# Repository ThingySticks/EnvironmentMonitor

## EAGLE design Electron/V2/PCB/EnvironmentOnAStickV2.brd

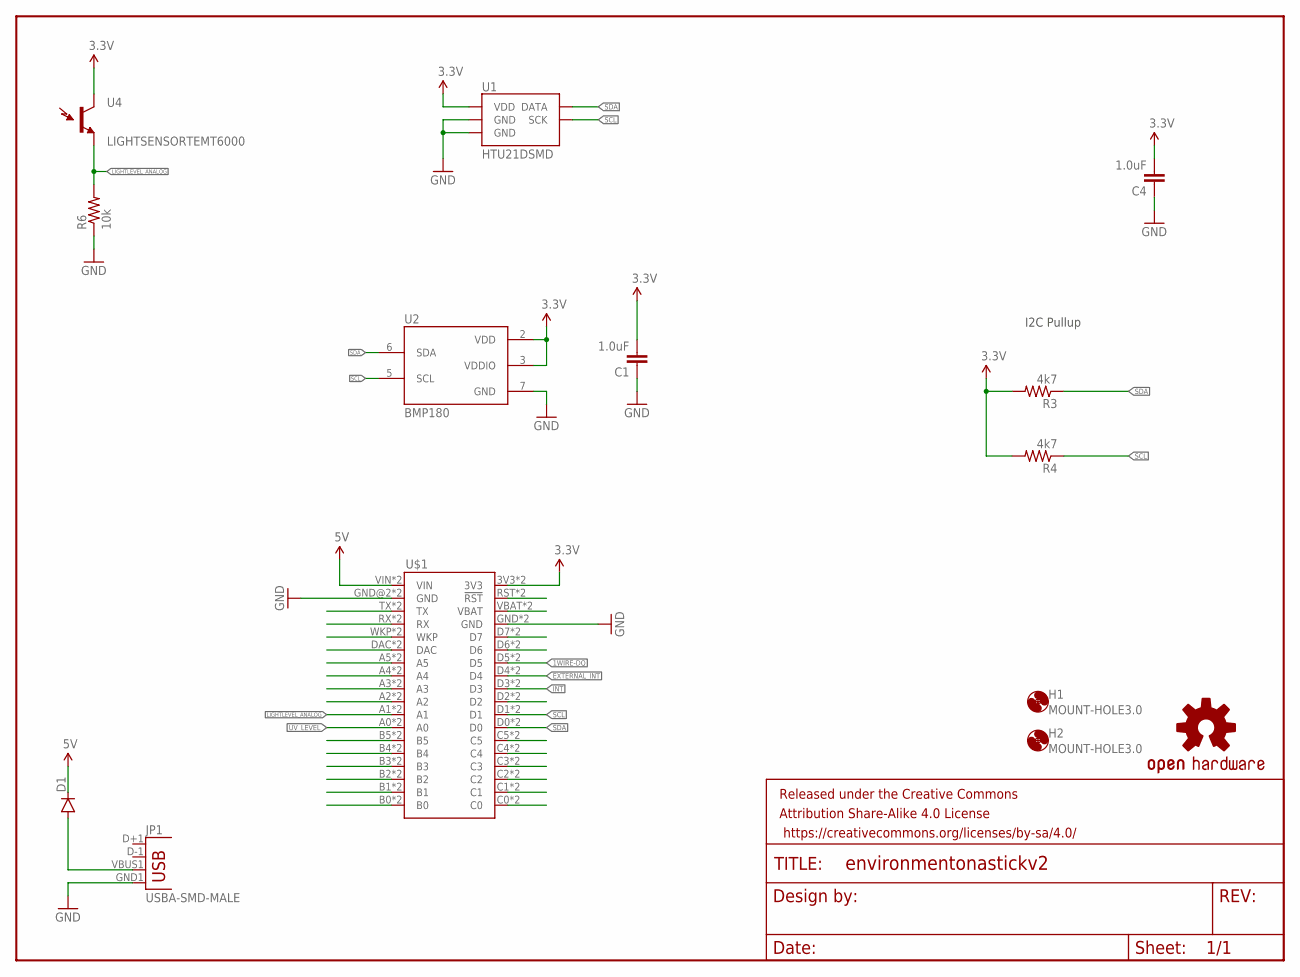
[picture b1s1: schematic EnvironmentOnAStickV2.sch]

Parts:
C1, C4: 1.0uF; 0805-CAP
D1: DIODESMA; SMA-DIODE
FRAME1: FRAME-LETTER; CREATIVE_COMMONS
H1, H2: MOUNT-HOLE3.0; 3,0
JP1: USBA-SMD-MALE; USB-A-SMT-MALE
LOGO1: OSHW-LOGOM; OSHW-LOGO-M
R3, R4: 4k7; 0805
R6: 10k; 0805
U1: HTU21DSMD; HTU21D
U2: BMP180
U4: LIGHTSENSORTEMT6000; TEMT6000-SEN
U$1: ELECTRONDUALNAMED; ELECTRON_SIMPLE_SILK_NAMES_DUAL

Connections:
1WIRE-DQ: U$1.D5, U$1.D5_1 (D5)
3.3V: C1.2, C4.2, R3.2, R4.2, U1.VDD, U2.2 (VDD), U2.3 (VDDIO), U4.COLLECTOR (C1), U$1.3V3, U$1.3V3_1 (3V3)
5V: D1.C, U$1.VIN, U$1.VIN_1B (VIN)
EXTERNAL_INT: U$1.D4, U$1.D4_1 (D4)
GND: C1.1, C4.1, JP1.GND1 (GND), R6.1, U1.7 (GND), U1.GND, U2.7 (GND), U$1.GND, U$1.GND@2 (GND), U$1.GND_1 (GND), U$1.GND_1B (GND)
INT: U$1.D3, U$1.D3_1 (D3)
LIGHTLEVEL_ANALOG: R6.2, U4.EMITTER (E1), U$1.A1, U$1.A1_1 (A1)
unnamed: U$1.RST (!RST), U$1.RST_1 (!RST)
unnamed: U$1.VBAT, U$1.VBATT_1 (VBAT)
unnamed: U$1.D7, U$1.D7_1 (D7)
unnamed: U$1.D6, U$1.D6_1 (D6)
unnamed: D1.A, JP1.VBUS1 (VBUS)
unnamed: U$1.D2, U$1.D2_1 (D2)
unnamed: U$1.C5, U$1.C5_1 (C5)
unnamed: U$1.C4, U$1.C4_1 (C4)
unnamed: U$1.C3, U$1.C3_1 (C3)
unnamed: U$1.C2, U$1.C2_1 (C2)
unnamed: U$1.C1, U$1.C1_1 (C1)
unnamed: U$1.C0, U$1.C0_1 (C0)
unnamed: U$1.B0, U$1.B0_1 (B0)
unnamed: U$1.B1, U$1.B1_1 (B1)
unnamed: U$1.B2, U$1.B2_1 (B2)
unnamed: U$1.B3, U$1.B3_1 (B3)
unnamed: U$1.B4, U$1.B4_1 (B4)
unnamed: U$1.B5, U$1.B5_1 (B5)
unnamed: U$1.A2, U$1.A2_1 (A2)
unnamed: U$1.A3, U$1.A3_1 (A3)
unnamed: U$1.A4, U$1.A4_1 (A4)
unnamed: U$1.A5, U$1.A5_1 (A5)
unnamed: U$1.DAC, U$1.DAC_1 (DAC)
unnamed: U$1.WKP, U$1.WKP_1 (WKP)
unnamed: U$1.RX, U$1.RX_1 (RX)
unnamed: U$1.TX, U$1.TX_1 (TX)
SCL: R4.1, U1.SCK, U2.5 (SCL), U$1.D1, U$1.D1_1 (D1)
SDA: R3.1, U1.DATA, U2.6 (SDA), U$1.D0, U$1.D0_1 (D0)
UV_LEVEL: U$1.A0, U$1.A0_1 (A0)

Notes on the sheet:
I2C Pullup

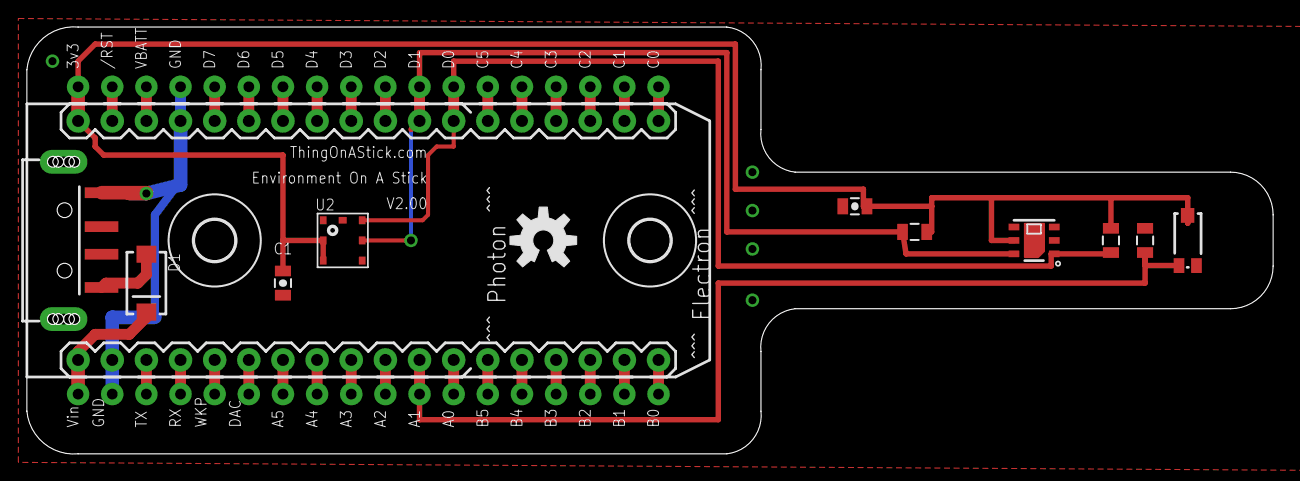
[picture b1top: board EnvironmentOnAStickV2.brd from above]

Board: 2 copper layers, 92.7 x 31.8 mm, 15 parts (0 on the bottom side), 36 nets.

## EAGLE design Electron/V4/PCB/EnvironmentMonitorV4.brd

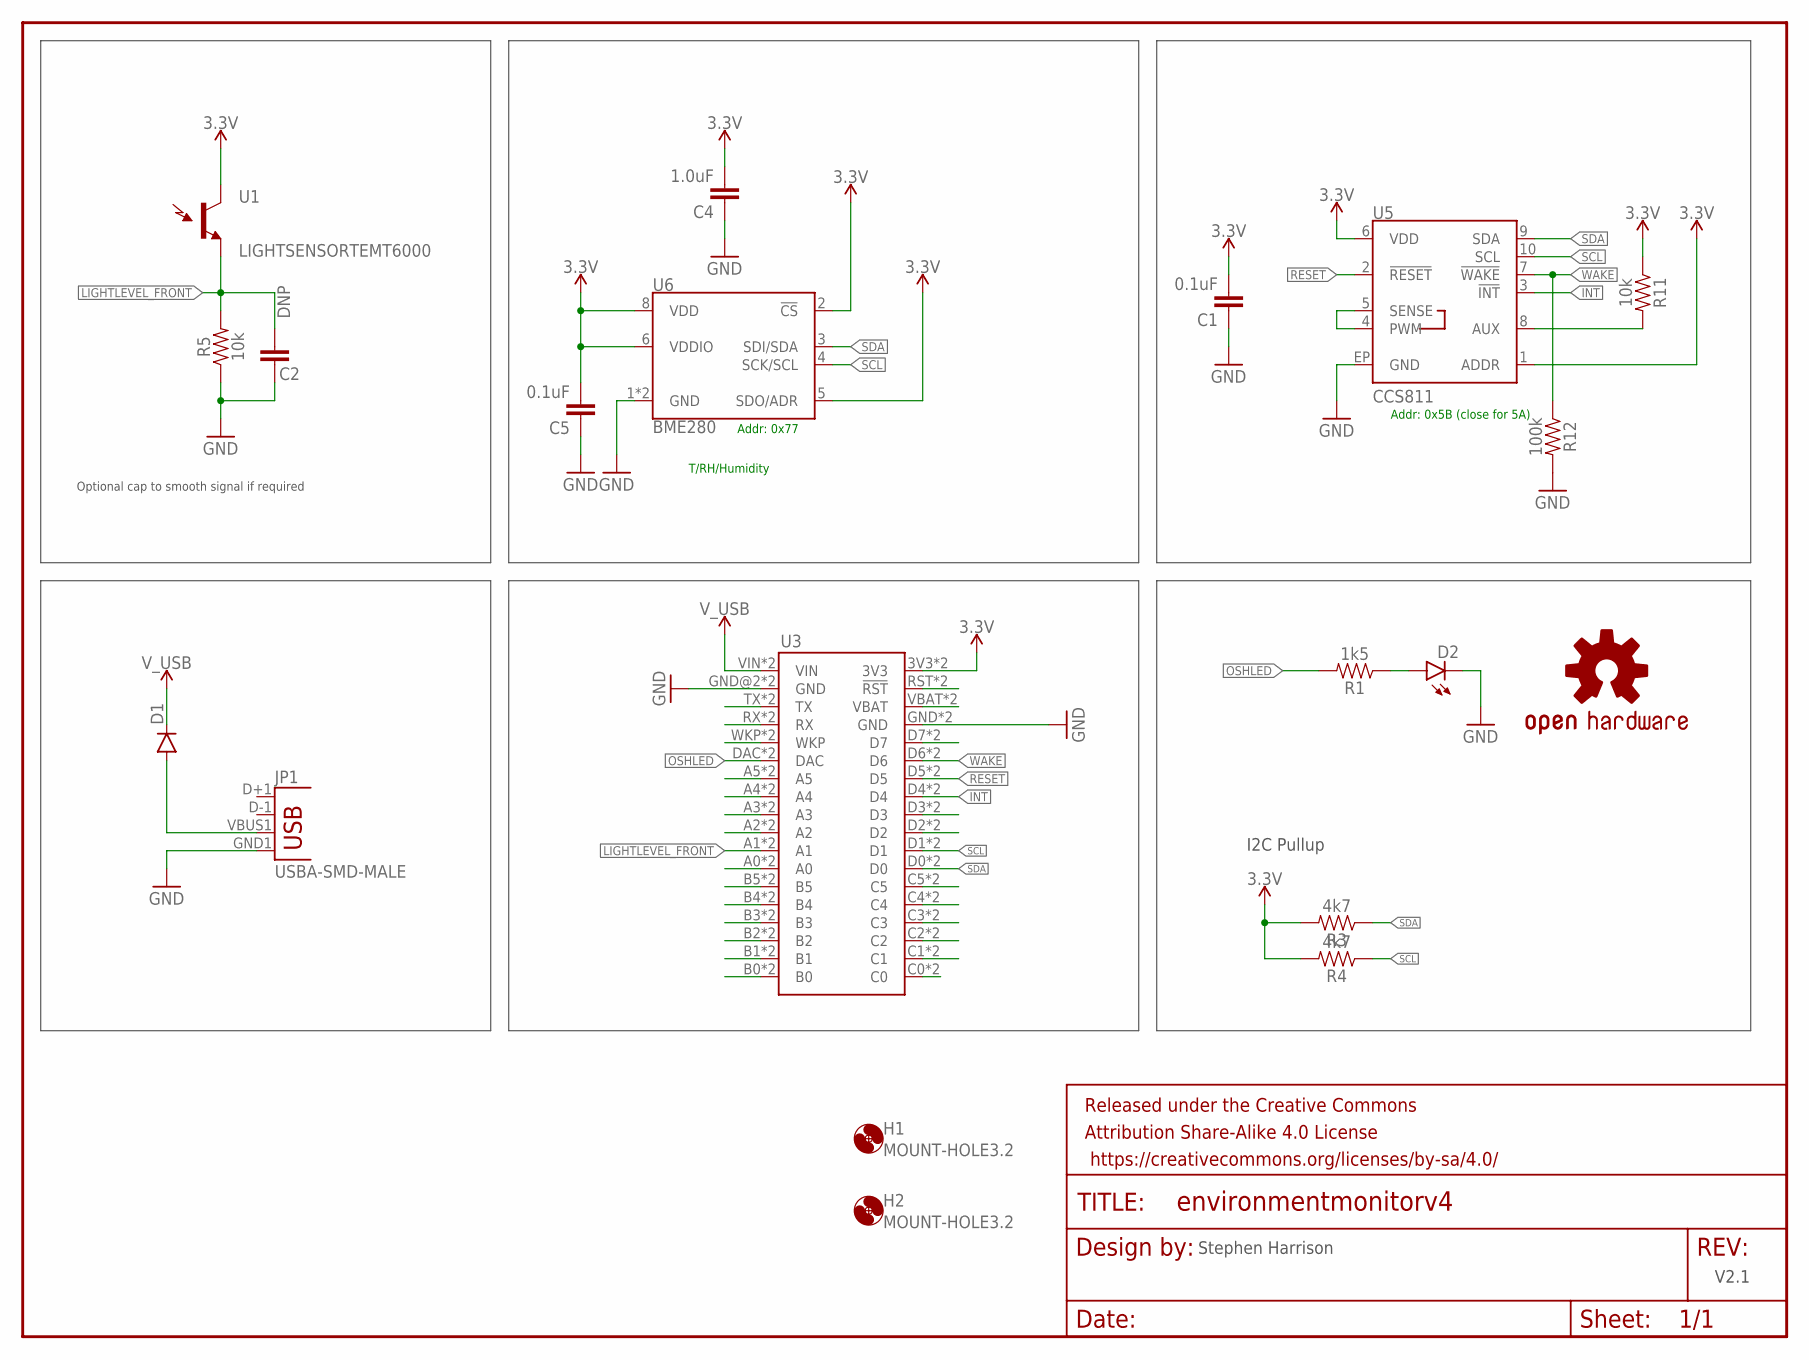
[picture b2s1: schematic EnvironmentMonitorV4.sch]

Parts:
C1, C5: 0.1uF; 0805-CAP
C2: DNP; 0805-CAP
C4: 1.0uF; 0805-CAP
D1: DIODESMA; SMA-DIODE
D2: LED1206-BOTTOM; LED-1206-BOTTOM
FRAME1: FRAME-LETTER; CREATIVE_COMMONS
H1, H2: MOUNT-HOLE3.2; 3,2
JP1: USBA-SMD-MALE; USB-A-SMT-MALE
LOGO1: OSHW-LOGOM; OSHW-LOGO-M
R1: 1k5; 0805
R3, R4: 4k7; 0805
R5, R11: 10k; 0805
R12: 100k; 0805
U1: LIGHTSENSORTEMT6000; TEMT6000-SEN
U3: ELECTRONDUALNAMED; ELECTRON_SIMPLE_SILK_NAMES_DUAL
U5: CCS811; LGA10
U6: BME280; LGA-8-2.5X2.5

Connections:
3.3V: C1.2, C4.2, C5.2, R3.2, R4.2, R11.1, U1.COLLECTOR (C1), U3.3V3, U3.3V3_1 (3V3), U5.1 (ADDR), U5.6 (VDD), U6.2 (!CS), U6.5 (SDO/ADR), U6.6 (VDDIO), U6.8 (VDD)
AUX: R11.2, U5.8 (AUX)
GND: C1.1, C2.1, C4.1, C5.1, D2.C, JP1.GND1 (GND), R5.1, R12.2, U3.GND, U3.GND@2 (GND), U3.GND_1 (GND), U3.GND_1B (GND), U5.EP (GND), U6.1 (GND), U6.7 (GND)
INT: U3.D4, U3.D4_1 (D4), U5.3 (!INT!)
LIGHTLEVEL_FRONT: C2.2, R5.2, U1.EMITTER (E1), U3.A1, U3.A1_1 (A1)
LIGHTLEVEL_REAR: U3.A0, U3.A0_1 (A0)
unnamed: U3.RST (!RST), U3.RST_1 (!RST)
unnamed: U3.VBAT, U3.VBATT_1 (VBAT)
unnamed: U3.WKP, U3.WKP_1 (WKP)
unnamed: D1.A, JP1.VBUS1 (VBUS)
unnamed: D2.A, R1.1
unnamed: U3.D7, U3.D7_1 (D7)
unnamed: U3.D2, U3.D2_1 (D2)
unnamed: U3.D3, U3.D3_1 (D3)
unnamed: U3.C5, U3.C5_1 (C5)
unnamed: U3.C4, U3.C4_1 (C4)
unnamed: U3.C3, U3.C3_1 (C3)
unnamed: U3.C2, U3.C2_1 (C2)
unnamed: U3.C1, U3.C1_1 (C1)
unnamed: U3.C0, U3.C0_1 (C0)
unnamed: U3.B0, U3.B0_1 (B0)
unnamed: U3.B1, U3.B1_1 (B1)
unnamed: U3.B2, U3.B2_1 (B2)
unnamed: U3.B3, U3.B3_1 (B3)
unnamed: U3.B4, U3.B4_1 (B4)
unnamed: U3.B5, U3.B5_1 (B5)
unnamed: U3.A2, U3.A2_1 (A2)
unnamed: U3.A3, U3.A3_1 (A3)
unnamed: U3.A4, U3.A4_1 (A4)
unnamed: U3.A5, U3.A5_1 (A5)
unnamed: U3.RX, U3.RX_1 (RX)
unnamed: U3.TX, U3.TX_1 (TX)
NTC_SENSE: U5.4 (PWM), U5.5 (SENSE)
OSHLED: R1.2, U3.DAC, U3.DAC_1 (DAC)
RESET: U3.D5, U3.D5_1 (D5), U5.2 (!RESET!)
SCL: R4.1, U3.D1, U3.D1_1 (D1), U5.10 (SCL), U6.4 (SCK/SCL)
SDA: R3.1, U3.D0, U3.D0_1 (D0), U5.9 (SDA), U6.3 (SDI/SDA)
V_USB: D1.C, U3.VIN, U3.VIN_1B (VIN)
WAKE: R12.1, U3.D6, U3.D6_1 (D6), U5.7 (!WAKE!)

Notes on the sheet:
I2C Pullup
V2.1
Stephen Harrison
T/RH/Humidity
Addr: 0x77
Addr: 0x5B (close for 5A)
Optional cap to smooth signal if required

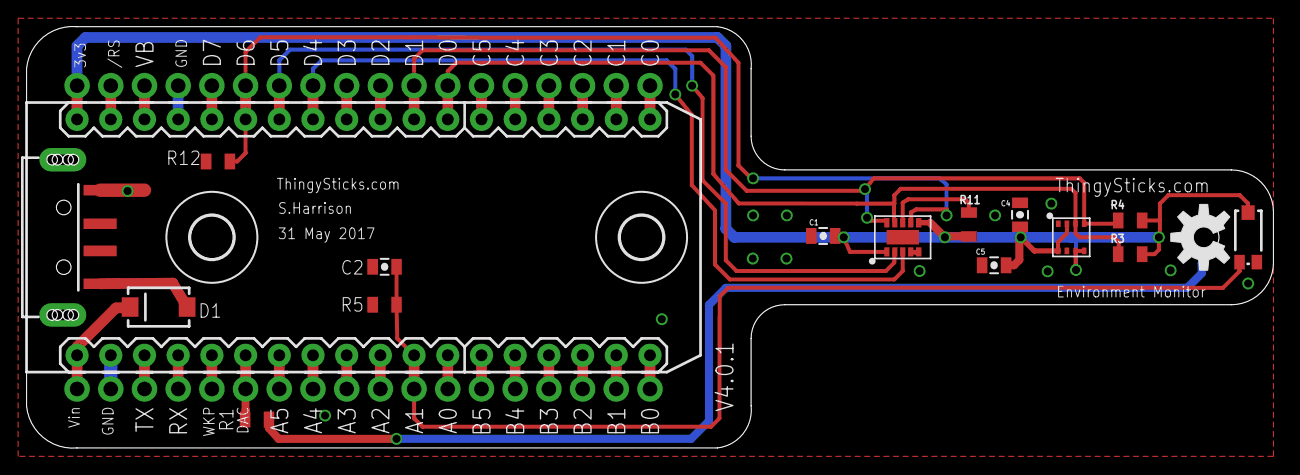
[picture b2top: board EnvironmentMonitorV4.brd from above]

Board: 2 copper layers, 94.0 x 31.8 mm, 21 parts (1 on the bottom side), 39 nets.

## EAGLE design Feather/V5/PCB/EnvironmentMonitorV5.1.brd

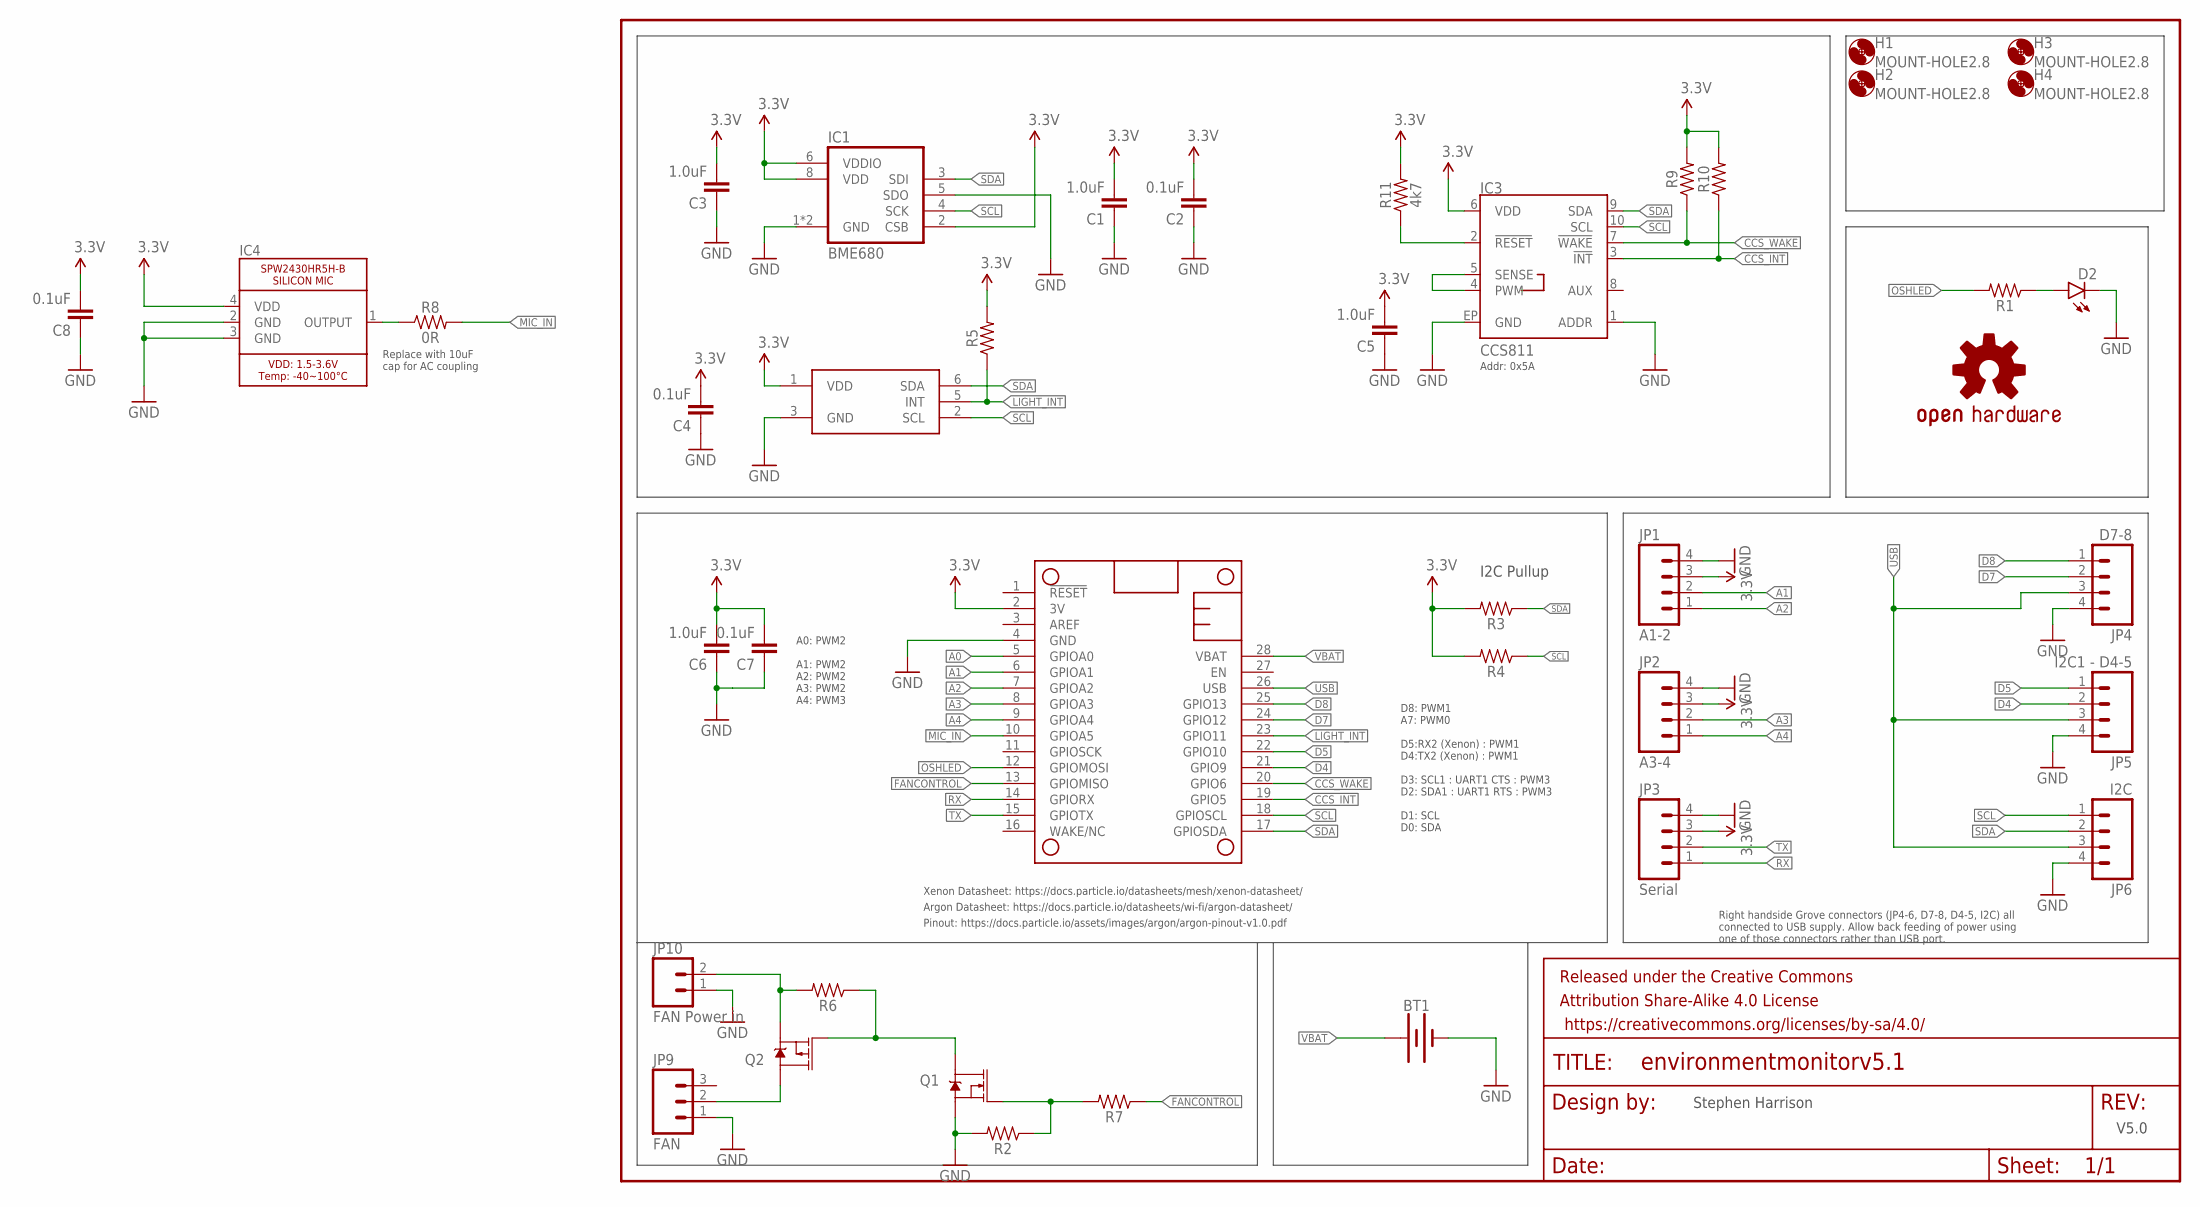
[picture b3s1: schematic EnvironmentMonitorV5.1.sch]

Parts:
BT1: BATTERY-16340; BATTERY_16340-HOLDER
C1, C3, C5, C6: 1.0uF; 0805-CAP
C2, C4, C7, C8: 0.1uF; 0805-CAP
D2: LED1206-BOTTOM; LED-1206-BOTTOM
FRAME1: FRAME-LETTER; CREATIVE_COMMONS
H1, H2, H3, H4: MOUNT-HOLE2.8; 2,8
IC1: BME680
IC2: TCS3472; FN-6
IC3: CCS811; LGA10
IC4: SPW2430HR5H-B
IC5: FEATHERWING_NODIM; FEATHERWING_DIM
JP1: A1-2; JST-4-PTH-VERT
JP2: A3-4; JST-4-PTH-VERT
JP3: Serial; JST-4-PTH-VERT
JP4: D7-8; JST-4-PTH-VERT
JP5: I2C1 - D4-5; JST-4-PTH-VERT
JP6: I2C; JST-4-PTH-VERT
JP9: FAN; MOLEX-1X3
JP10: FAN Power in; MOLEX-1X2_LOCK
LOGO1: OSHW-LOGOM; OSHW-LOGO-M
Q1: 220mA/50V/3.5Ω; SOT23-3
Q2: 4.3A/20V/54mΩ; SOT23-3
R1, R2, R3, R4, R5, R6, R7, R9, R10: 0805
R8: 0R; 0805
R11: 4k7; 0805

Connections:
3.3V: C1.2, C2.2, C3.2, C4.2, C5.2, C6.2, C7.2, C8.2, IC1.2 (CSB), IC1.6 (VDDIO), IC1.8 (VDD), IC2.1 (VDD), IC3.6 (VDD), IC4.4 (VDD), IC5.2 (3V), JP1.3, JP2.3, JP3.3, R3.2, R4.2, R5.2, R9.2, R10.2, R11.2
A0: IC5.5 (GPIOA0)
A1: IC5.6 (GPIOA1), JP1.2
A2: IC5.7 (GPIOA2), JP1.1
A3: IC5.8 (GPIOA3), JP2.2
A4: IC5.9 (GPIOA4), JP2.1
CCS8_RESET: IC3.2 (!RESET!), R11.1
CCS_INT: IC3.3 (!INT!), IC5.19 (GPIO5), R10.1
CCS_WAKE: IC3.7 (!WAKE!), IC5.20 (GPIO6), R9.1
D4: IC5.21 (GPIO9), JP5.2
D5: IC5.22 (GPIO10), JP5.1
D7: IC5.24 (GPIO12), JP4.2
D8: IC5.25 (GPIO13), JP4.1
FANCONTROL: IC5.13 (GPIOMISO), R7.1
GND: BT1.P$2 (-), C1.1, C2.1, C3.1, C4.1, C5.1, C6.1, C7.1, C8.1, D2.C, IC1.1 (GND), IC1.5 (SDO), IC1.7 (GND), IC2.3 (GND), IC3.1 (ADDR), IC3.EP (GND), IC4.2 (GND), IC4.3 (GND), IC5.4 (GND), JP1.4, JP2.4, JP3.4, JP4.4, JP5.4, JP6.4, JP9.1, JP10.1, Q1.2 (S), R2.2
LIGHT_INT: IC2.5 (INT), IC5.23 (GPIO11), R5.1
MIC_IN: IC5.10 (GPIOA5), R8.2
unnamed: JP10.2, Q2.2 (S), R6.2
unnamed: Q1.3 (D), Q2.1 (G), R6.1
unnamed: IC3.4 (PWM), IC3.5 (SENSE)
unnamed: Q1.1 (G), R2.1, R7.2
unnamed: D2.A, R1.1
unnamed: IC4.1 (OUTPUT), R8.1
unnamed: JP9.2, Q2.3 (D)
OSHLED: IC5.12 (GPIOMOSI), R1.2
RX: IC5.14 (GPIORX), JP3.1
SCL: IC1.4 (SCK), IC2.2 (SCL), IC3.10 (SCL), IC5.18 (GPIOSCL), JP6.1, R4.1
SDA: IC1.3 (SDI), IC2.6 (SDA), IC3.9 (SDA), IC5.17 (GPIOSDA), JP6.2, R3.1
TX: IC5.15 (GPIOTX), JP3.2
USB: IC5.26 (USB), JP4.3, JP5.3, JP6.3
VBAT: BT1.P$1 (+), IC5.28 (VBAT)

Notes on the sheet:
I2C Pullup
V5.0
Stephen Harrison
Xenon Datasheet: https://docs.particle.io/datasheets/mesh/xenon-datasheet/
Argon Datasheet: https://docs.particle.io/datasheets/wi-fi/argon-datasheet/
Pinout: https://docs.particle.io/assets/images/argon/argon-pinout-v1.0.pdf
A0: PWM2 A1: PWM2 A2: PWM2 A3: PWM2 A4: PWM3
D8: PWM1 A7: PWM0 D5:RX2 (Xenon) : PWM1 D4:TX2 (Xenon) : PWM1 D3: SCL1 : UART1 CTS : PWM3 D2: SDA1 : UART1 RTS : PWM3 D1: SCL D0: SDA
Replace with 10uF cap for AC coupling
Addr: 0x5A
Right handside Grove connectors (JP4-6, D7-8, D4-5, I2C) all connected to USB supply. Allow back feeding of power using one of those connectors rather than USB port.

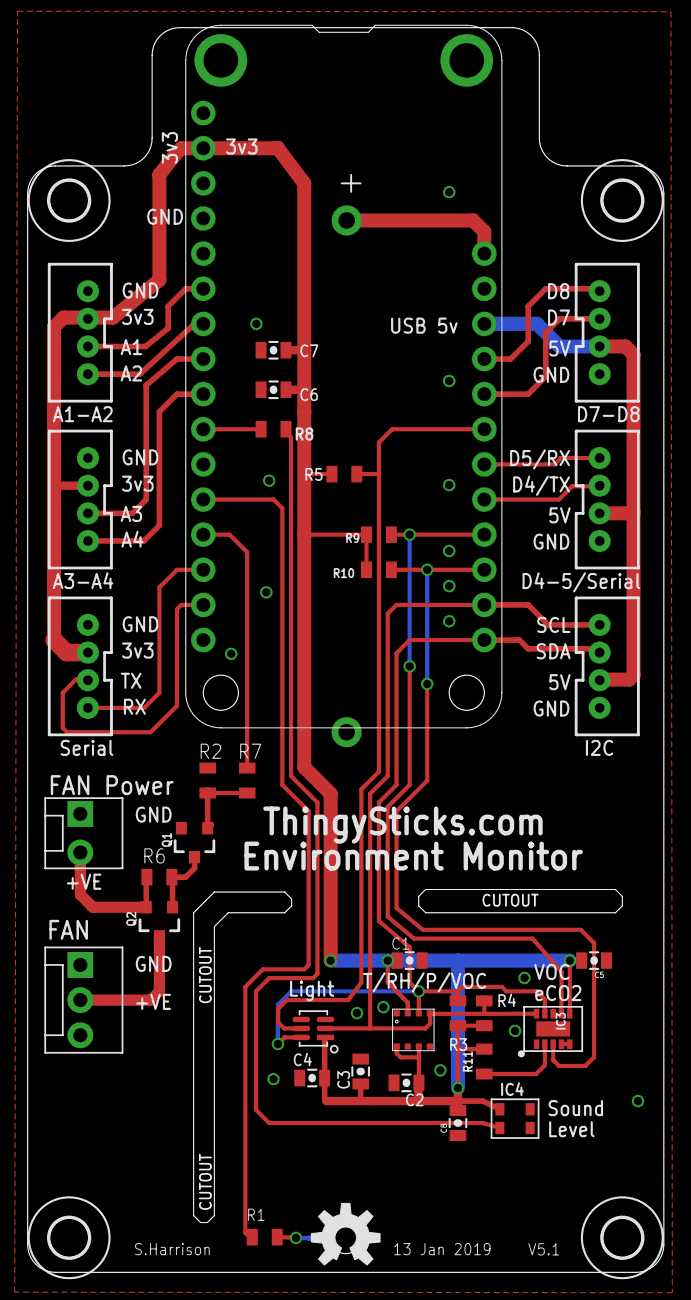
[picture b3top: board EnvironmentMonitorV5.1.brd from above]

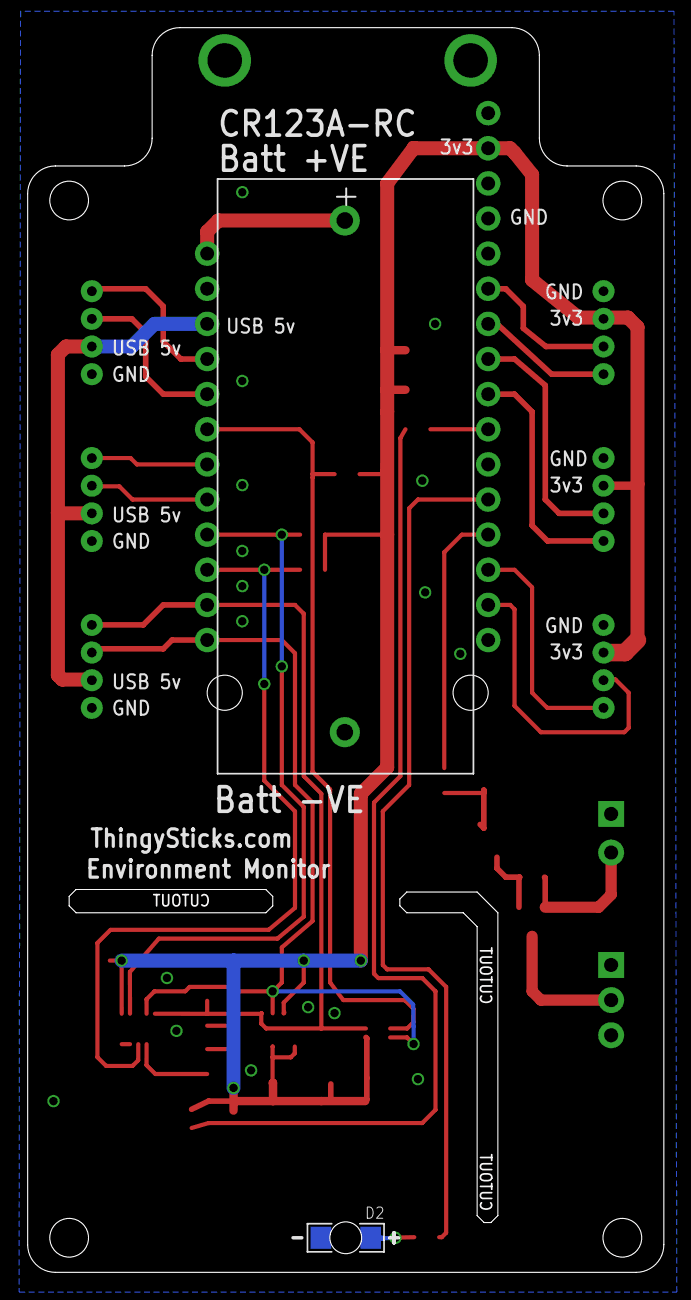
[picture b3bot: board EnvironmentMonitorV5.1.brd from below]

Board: 2 copper layers, 46.0 x 90.0 mm, 42 parts (2 on the bottom side), 30 nets.

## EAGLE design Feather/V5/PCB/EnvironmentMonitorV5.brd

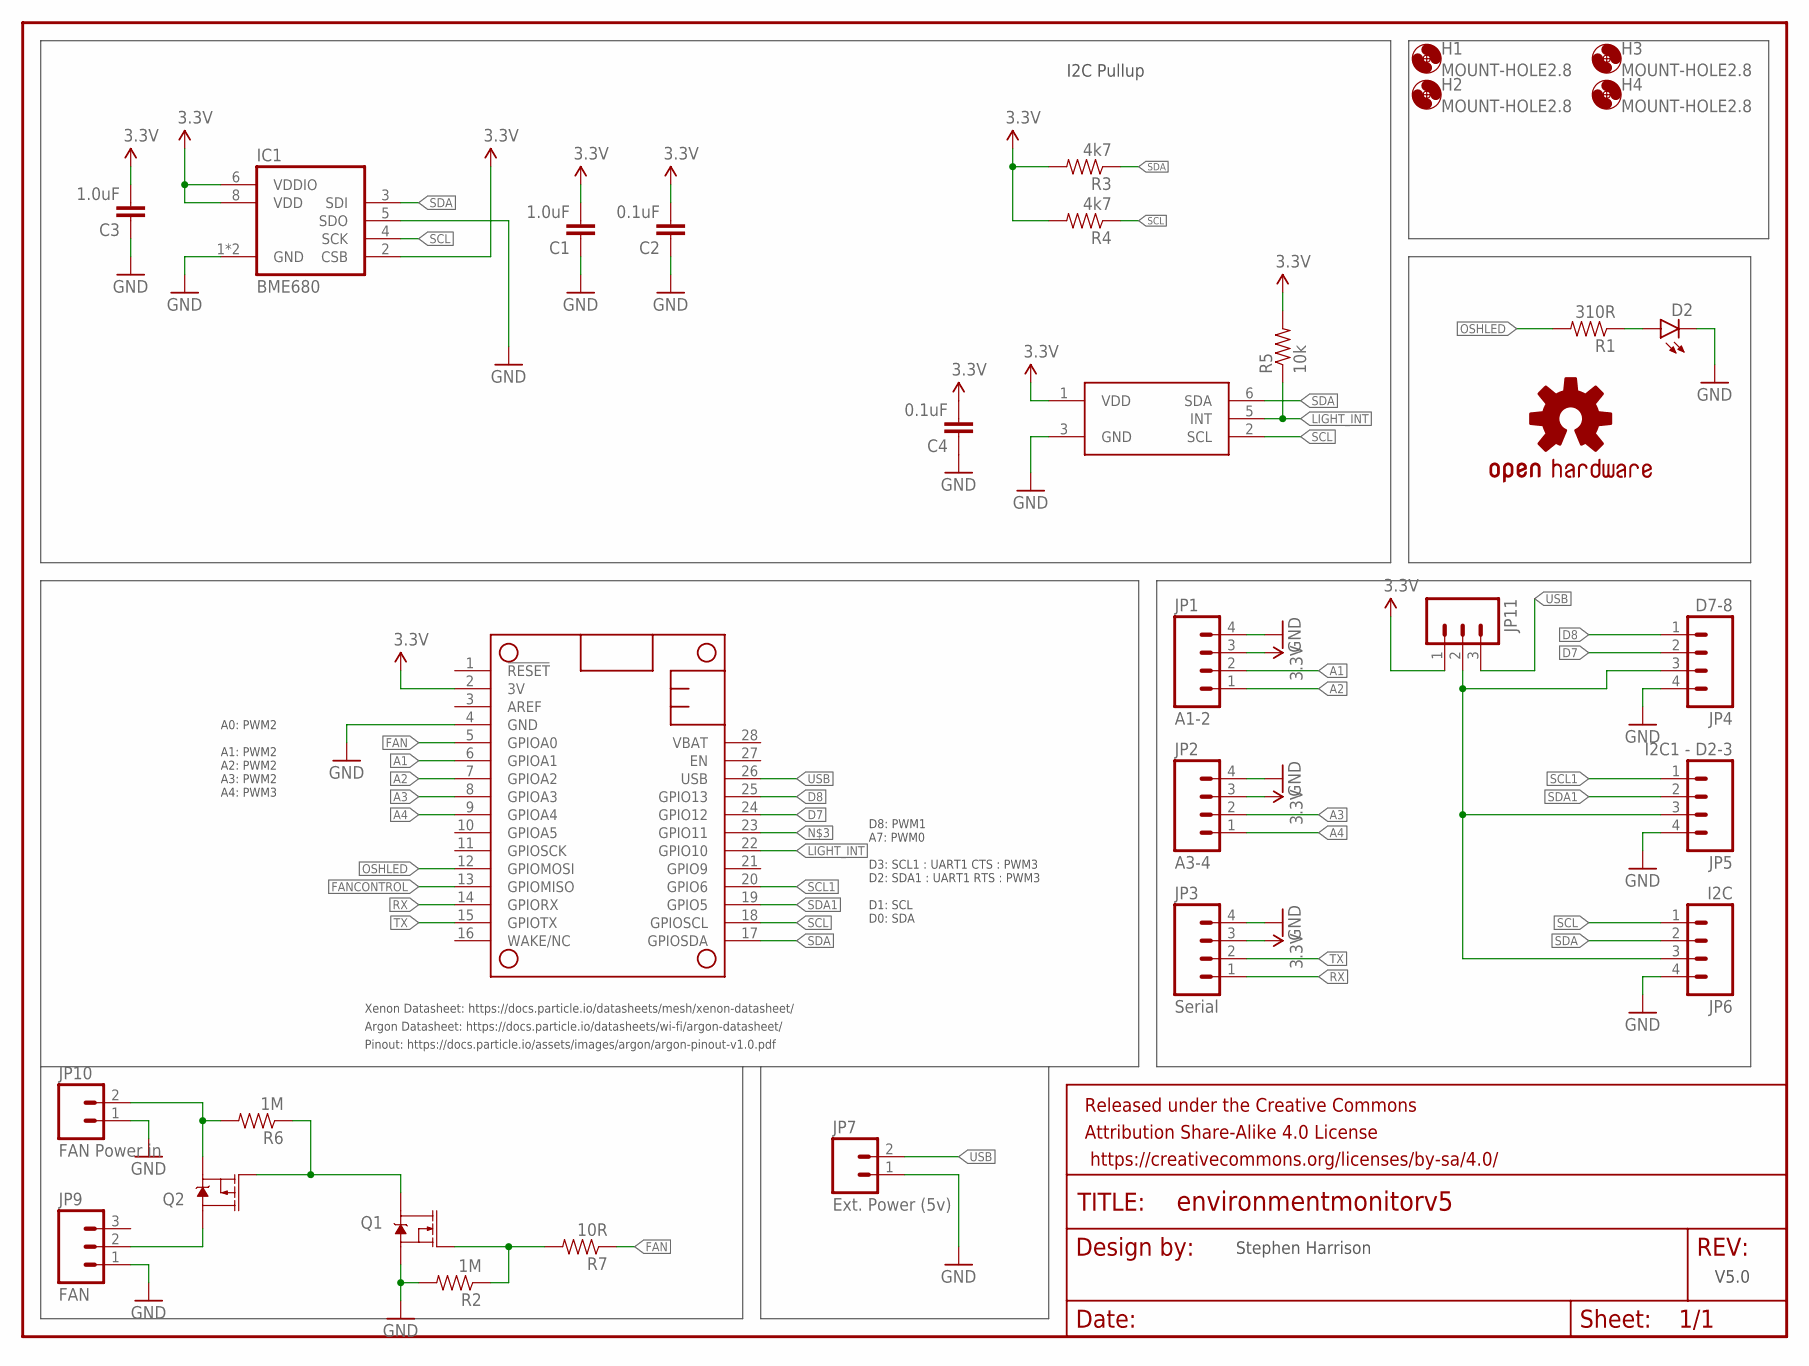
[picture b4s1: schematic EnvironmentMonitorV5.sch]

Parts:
C1, C3: 1.0uF; 0805-CAP
C2, C4: 0.1uF; 0805-CAP
D2: LED1206-BOTTOM; LED-1206-BOTTOM
FRAME1: FRAME-LETTER; CREATIVE_COMMONS
H1, H2, H3, H4: MOUNT-HOLE2.8; 2,8
IC1: BME680
IC2: TCS3472; FN-6
JP1: A1-2; JST-4-PTH-VERT
JP2: A3-4; JST-4-PTH-VERT
JP3: Serial; JST-4-PTH-VERT
JP4: D7-8; JST-4-PTH-VERT
JP5: I2C1 - D2-3; JST-4-PTH-VERT
JP6: I2C; JST-4-PTH-VERT
JP7: Ext. Power (5v); MOLEX-1X2_LOCK
JP9: FAN; MOLEX-1X3
JP10: FAN Power in; MOLEX-1X2_LOCK
JP11: M03PTH; 1X03
LOGO1: OSHW-LOGOM; OSHW-LOGO-M
MS1: FEATHERWING_NODIM; FEATHERWING_DIM
Q1: 220mA/50V/3.5Ω; SOT23-3
Q2: 4.3A/20V/54mΩ; SOT23-3
R1: 310R; 0805
R2, R6: 1M; 0805
R3, R4: 4k7; 0805
R5: 10k; 0805
R7: 10R; 0805

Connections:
3.3V: C1.2, C2.2, C3.2, C4.2, IC1.2 (CSB), IC1.6 (VDDIO), IC1.8 (VDD), IC2.1 (VDD), JP1.3, JP2.3, JP3.3, JP11.1, MS1.2 (3V), R3.2, R4.2, R5.2
A1: JP1.2, MS1.6 (GPIOA1)
A2: JP1.1, MS1.7 (GPIOA2)
A3: JP2.2, MS1.8 (GPIOA3)
A4: JP2.1, MS1.9 (GPIOA4)
D7: JP4.2, MS1.24 (GPIO12)
D8: JP4.1, MS1.25 (GPIO13)
FAN: MS1.5 (GPIOA0), R7.1
FANCONTROL: MS1.13 (GPIOMISO)
GND: C1.1, C2.1, C3.1, C4.1, D2.C, IC1.1 (GND), IC1.5 (SDO), IC1.7 (GND), IC2.3 (GND), JP1.4, JP2.4, JP3.4, JP4.4, JP5.4, JP6.4, JP7.1, JP9.1, JP10.1, MS1.4 (GND), Q1.2 (S), R2.2
LIGHT_INT: IC2.5 (INT), MS1.22 (GPIO10), R5.1
unnamed: JP10.2, Q2.2 (S), R6.2
unnamed: Q1.3 (D), Q2.1 (G), R6.1
unnamed: JP4.3, JP5.3, JP6.3, JP11.2
unnamed: Q1.1 (G), R2.1, R7.2
unnamed: D2.A, R1.1
unnamed: JP9.2, Q2.3 (D)
OSHLED: MS1.12 (GPIOMOSI), R1.2
RX: JP3.1, MS1.14 (GPIORX)
SCL: IC1.4 (SCK), IC2.2 (SCL), JP6.1, MS1.18 (GPIOSCL), R4.1
SCL1: JP5.1, MS1.20 (GPIO6)
SDA: IC1.3 (SDI), IC2.6 (SDA), JP6.2, MS1.17 (GPIOSDA), R3.1
SDA1: JP5.2, MS1.19 (GPIO5)
TX: JP3.2, MS1.15 (GPIOTX)
USB: JP7.2, JP11.3, MS1.26 (USB)

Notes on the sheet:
I2C Pullup
V5.0
Stephen Harrison
Xenon Datasheet: https://docs.particle.io/datasheets/mesh/xenon-datasheet/
Argon Datasheet: https://docs.particle.io/datasheets/wi-fi/argon-datasheet/
Pinout: https://docs.particle.io/assets/images/argon/argon-pinout-v1.0.pdf
A0: PWM2 A1: PWM2 A2: PWM2 A3: PWM2 A4: PWM3
D8: PWM1 A7: PWM0 D3: SCL1 : UART1 CTS : PWM3 D2: SDA1 : UART1 RTS : PWM3 D1: SCL D0: SDA

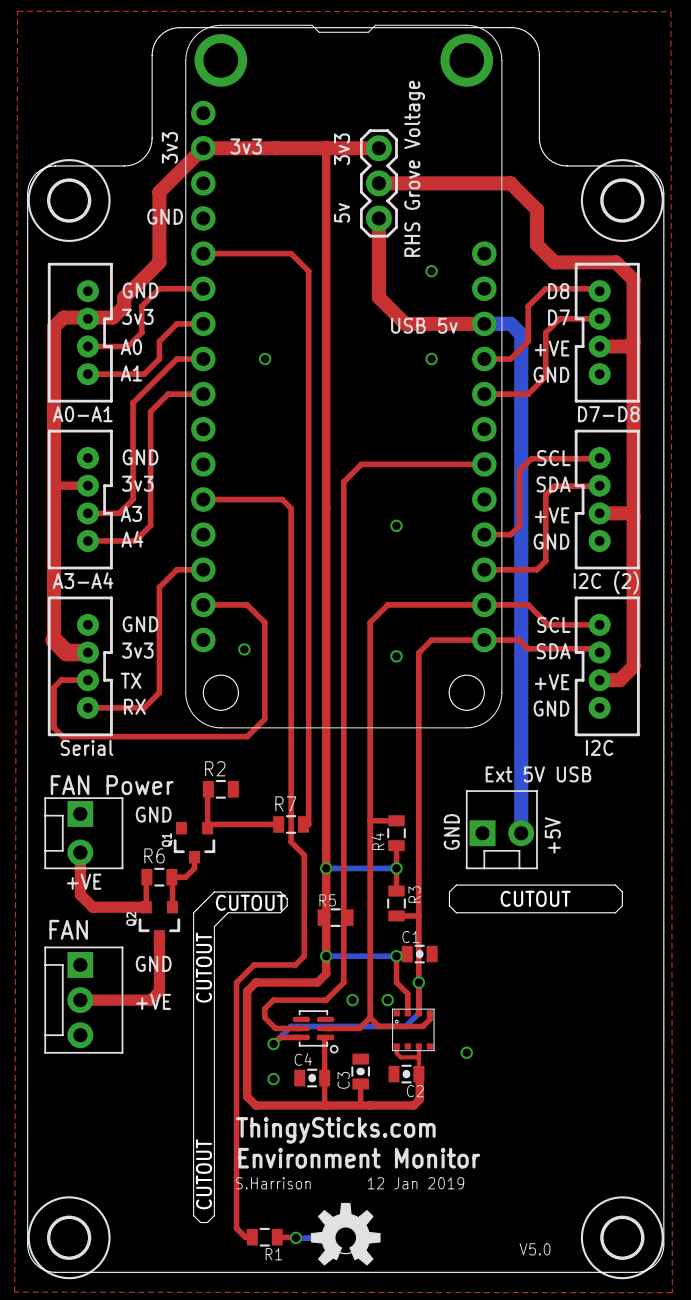
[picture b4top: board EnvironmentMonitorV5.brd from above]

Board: 2 copper layers, 46.0 x 90.0 mm, 33 parts (1 on the bottom side), 24 nets.

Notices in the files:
parts and their libraries:
SparkFun-Sensors: Licensing: Creative Commons ShareAlike 4.0 International - https://creativecommons.org/licenses/by-sa/4.0
SparkFun-Aesthetics: Released under the Creative Commons Attribution Share-Alike 4.0 License
SparkFun-Aesthetics: https://creativecommons.org/licenses/by-sa/4.0
